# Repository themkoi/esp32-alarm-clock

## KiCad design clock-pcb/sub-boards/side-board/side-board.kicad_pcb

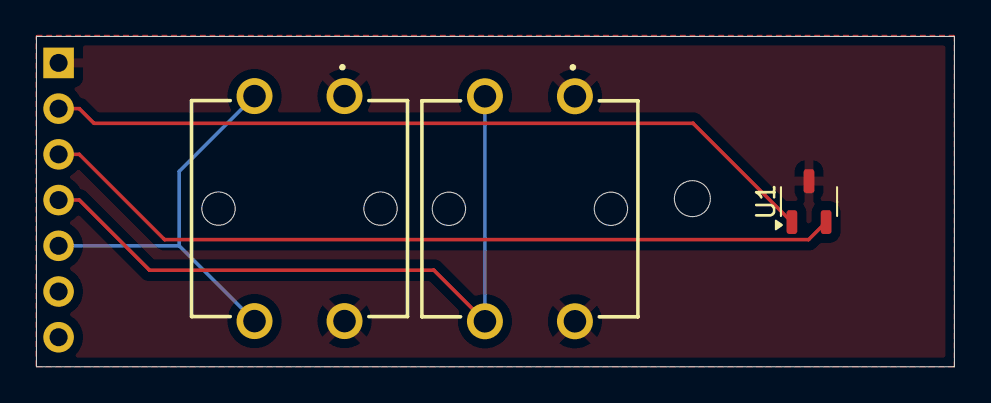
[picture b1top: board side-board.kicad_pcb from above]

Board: 2 copper layers, 51.0 x 18.3 mm, 4 parts (1 on the bottom side), 5 nets.

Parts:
J1: Conn_01x07_Socket; PinHeader_1x07_P2.54mm_Horizontal
S1, S2: B3F-5050; B3F-4055
U1: TMAG5231C1GQDBZR; SOT-23-3

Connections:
+3V3: J1.2, U1.1 (VCC)
GND: J1.1, S1.1 (COM_1), S1.2 (COM_2), S2.1 (COM_1), S2.2 (COM_2), U1.3 (GND)
GPIO14: J1.4, S2.3 (NO_1), S2.4 (NO_2)
GPIO15: J1.5, S1.3 (NO_1), S1.4 (NO_2)
GPIO35: J1.3, U1.2 (OUT)

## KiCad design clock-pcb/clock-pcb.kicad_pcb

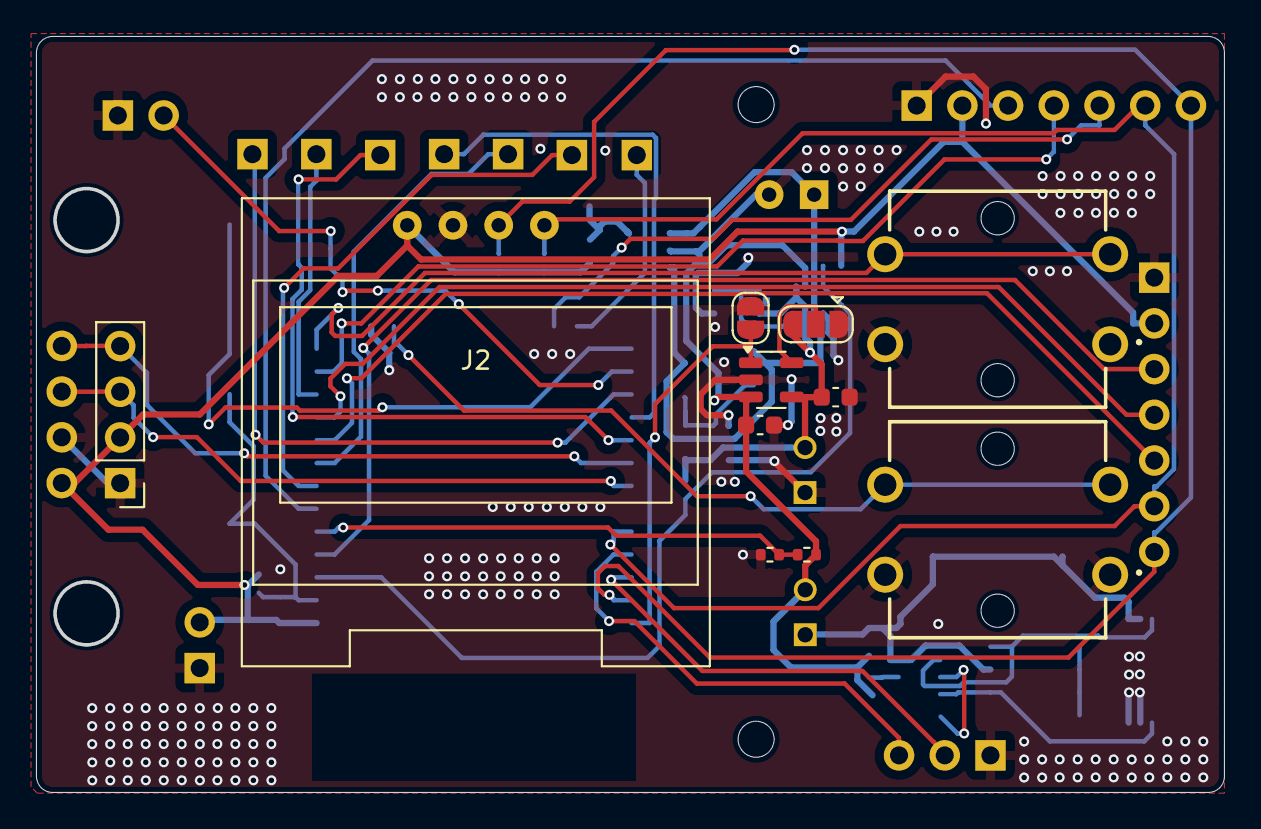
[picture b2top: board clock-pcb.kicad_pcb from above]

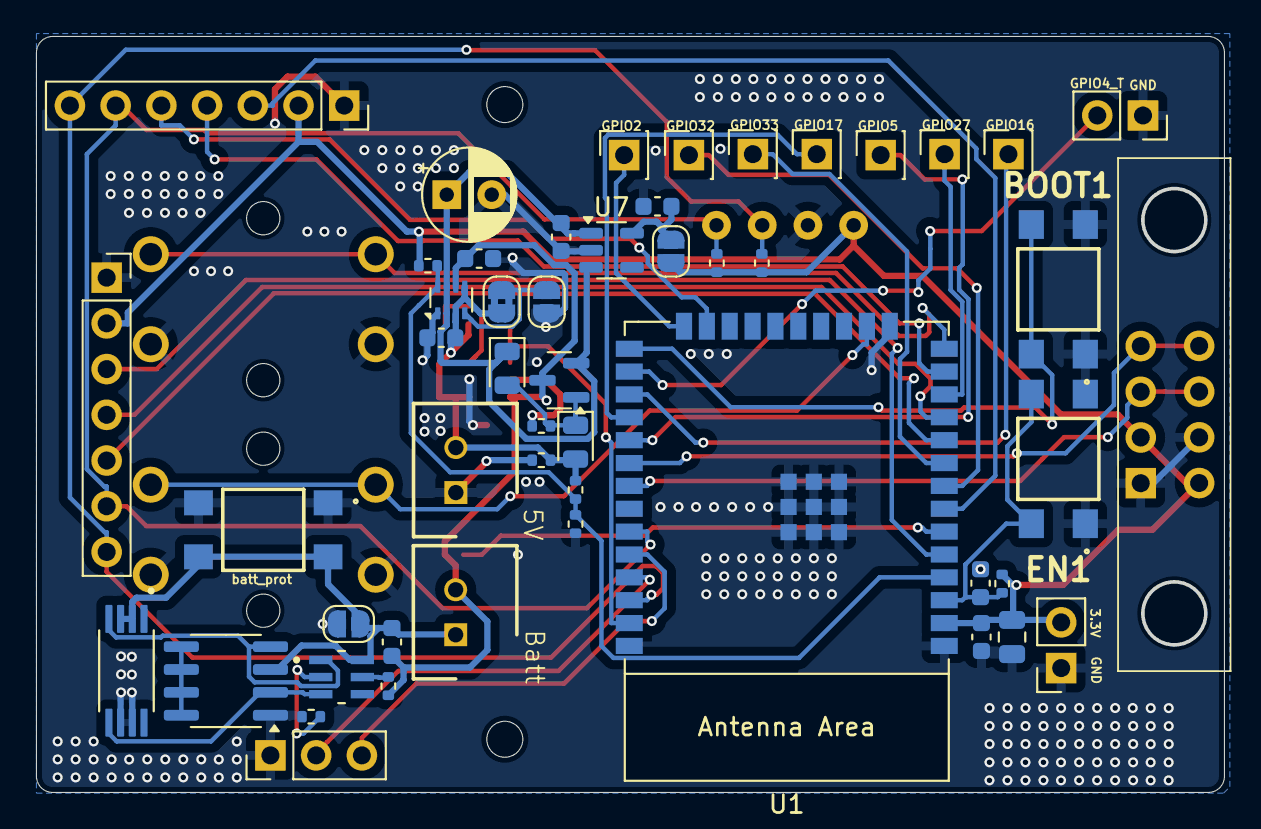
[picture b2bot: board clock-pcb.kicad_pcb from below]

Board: 2 copper layers, 66.0 x 42.0 mm, 61 parts (49 on the bottom side), 42 nets.

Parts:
AO9926C1: SOIC-8_3.9x4.9mm_P1.27mm
BATT_P1: TL3305AF160QG
BOOT1: TL3305AF160QG
C1: 22uF; C_0805_2012Metric
C2, C3, C4: 0.1uF; C_0603_1608Metric
C5: 100uF; CP_Radial_D5.0mm_P2.50mm
C6, C7, C8, C9, C10, C11: 1uF; C_0603_1608Metric
D3, D4: SD0805S040S0R5; D_0805_2012Metric
EN1: TL3305AF160QG
J1: Conn_01x03_Pin; PinHeader_1x03_P2.54mm_Vertical
J2: oled; SSD1306_0.96_Oled
J3: Led display; tm1637_module
J4: Led display 2; PinHeader_1x04_P2.54mm_Vertical
J5, J6: Conn_01x07_Socket; PinSocket_1x07_P2.54mm_Vertical
J7, J9, J10, J11, J12, J13, J14: Conn_01x01_Socket; PinSocket_1x01_P2.54mm_Vertical
J8, J15: Conn_01x02_Socket; PinSocket_1x02_P2.54mm_Vertical
JP1, JP2, JP7: Jumper; SolderJumper-2_P1.3mm_Open_RoundedPad1.0x1.5mm
JP3: Jumper_bridged; SolderJumper-2_P1.3mm_Bridged2Bar_RoundedPad1.0x1.5mm
JP4: SolderJumper_3_Open; SolderJumper-3_P1.3mm_Open_RoundedPad1.0x1.5mm
JP5: SolderJumper_2_Open; SolderJumper-2_P1.3mm_Open_RoundedPad1.0x1.5mm
Q1: FS8205A; SOP65P640X120-8N
Q2: FDN304PZ; SOT-23
R1: 10k; R_0402_1005Metric
R2: 300k; R_0402_1005Metric
R3, R10: 800k; R_0402_1005Metric
R4: 330R; R_0402_1005Metric
R5: 2.7K; R_0402_1005Metric
R6: 10K; R_0402_1005Metric
R7: 500k; R_0402_1005Metric
R8: 100K; R_0402_1005Metric
R9: 50k; R_0402_1005Metric
R11, R12: 5.1k; R_0402_1005Metric
S3, S4: B3F-5050; B3F-4055
U1: ESP32-WROOM-E; ESP32-WROOM-32E
U2: SOT95P280X140-6N
U3: SHDR2W64P0X250_1X2_740X575X700P
U4: TPS2116DRL; SOT-583-8
U5: MCP73811T-420I-OT; SOT-23-5
U7: TLV75533PDBV; SOT-23-5
USB_BOARD1: Conn_01x02_Socket; SHDR2W64P0X250_1X2_740X575X700P

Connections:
+3V3: C1.1, C2.1, J2.1, J3.4, J4.2, J5.2, J6.2, J15.2, JP7.2 (B), R1.1, R6.2, R11.1, R12.1, U1.2 (3V3)
+BATT: C4.2, C7.1, C11.1, Q2.3 (D), R2.1, R4.2, U3.2, U4.6 (VIN2), U5.3 (V_{BAT})
-BATT: AO9926C1.3 (S1), BATT_P1.3, BATT_P1.4, C4.1, JP1.1 (A), Q1.2, Q1.3, U2.6 (VSS), U3.1
ADC_BATT: R2.2, R3.1, U1.6 (GPIO34/ADC1_CH6)
BUTTON_DOWN: S4.3 (NO_1), S4.4 (NO_2), U1.16 (MTCK/GPIO13/ADC2_CH4)
BUTTON_UP: S3.3 (NO_1), S3.4 (NO_2), U1.14 (MTDI/GPIO12/ADC2_CH5)
CHARGE_EN: JP5.2 (B), U1.37 (GPIO23), U5.1 (CE)
CLK: J3.1, J4.4, U1.30 (GPIO18)
CO: AO9926C1.2 (G2), Q1.5, U2.3 (CO)
DIO: J3.2, J4.3, U1.31 (GPIO19)
DO: AO9926C1.4 (G1), Q1.4, U2.1 (DO)
EN: C3.2, EN1.3, EN1.4, R1.2, U1.3 (EN/CHIP_PU)
GND: AO9926C1.1 (S2), BATT_P1.1, BATT_P1.2, BOOT1.1, BOOT1.2, C1.2, C2.2, C3.1, C5.2, C6.1, C7.2, C8.2, C9.2, C10.2, C11.2, EN1.1, EN1.2, J1.1, J2.2, J3.3, J4.1, J5.1, J6.1, J8.1, J15.1, JP1.2 (B), JP2.1 (A), JP4.1 (A), JP5.1 (A), Q1.6, Q1.7, R3.2, R5.2, R8.2, R9.2, R10.2, S3.1 (COM_1), S3.2 (COM_2), S4.1 (COM_1), S4.2 (COM_2), U1.1 (GND), U1.15 (GND), U1.38 (GND), U1.39 (GND_THERMAL), U4.1 (GND), U5.2 (V_{SS}), U7.2 (GND), USB_BOARD1.1
GPIO4_T: J8.2, U1.26 (ADC2_CH0/GPIO4)
GPIO14: J5.4, U1.13 (MTMS/GPIO14/ADC2_CH6)
GPIO15: J5.5, U1.23 (MTDO/GPIO15/ADC2_CH3)
GPIO25: J6.5, U1.10 (DAC_1/ADC2_CH8/GPIO25)
GPIO26: J6.4, U1.11 (DAC_2/ADC2_CH9/GPIO26)
GPIO35: J5.3, U1.7 (GPIO35/ADC1_CH7)
GPIO39: J6.3, U1.5 (SENSOR_VN/GPIO39/ADC1_CH3)
IO0: BOOT1.3, BOOT1.4, U1.25 (GPIO0/BOOT/ADC2_CH1)
LDO_IN: C5.1, C9.1, D4.1 (K), Q2.2 (S), U4.2 (VOUT), U4.7 (VOUT), U7.1 (IN), U7.3 (EN)
unnamed: AO9926C1.5 (D1), AO9926C1.6 (D1), AO9926C1.7 (D2), AO9926C1.8 (D2)
unnamed: D3.1 (K), D4.2 (A), Q2.1 (G), R8.1
unnamed: J7.1, U1.8 (32K_XP/GPIO32/ADC1_CH4)
unnamed: J9.1, U1.29 (GPIO5)
unnamed: J10.1, U1.24 (ADC2_CH2/GPIO2)
unnamed: J11.1, U1.12 (ADC2_CH7/GPIO27)
unnamed: J12.1, U1.27 (GPIO16)
unnamed: J13.1, U1.28 (GPIO17)
unnamed: J14.1, U1.9 (32K_XN/GPIO33/ADC1_CH5)
unnamed: JP2.2 (B), JP3.1 (A), U4.4 (PR1)
unnamed: JP4.2 (C), U5.5 (PROG)
unnamed: C8.1, JP7.1 (A), U7.5 (OUT)
unnamed: R4.1, U2.5 (VDD)
unnamed: R5.1, U2.2 (VM)
POWER_STATUS: R6.1, R7.2, R10.1, U1.4 (SENSOR_VP/GPIO36/ADC1_CH0), U4.8 (ST)
RX: J1.3, U1.34 (U0RXD/GPIO3)
SCL: J2.3, J5.7, J6.7, R11.2, U1.36 (GPIO22)
SDA: J2.4, J5.6, J6.6, R12.2, U1.33 (GPIO21)
TX: J1.2, U1.35 (U0TXD/GPIO1)
VBUS: C6.2, C10.1, D3.2 (A), JP3.2 (B), JP4.3 (B), R7.1, R9.1, U4.3 (VIN1), U4.5 (MODE), U5.4 (V_{DD}), USB_BOARD1.2

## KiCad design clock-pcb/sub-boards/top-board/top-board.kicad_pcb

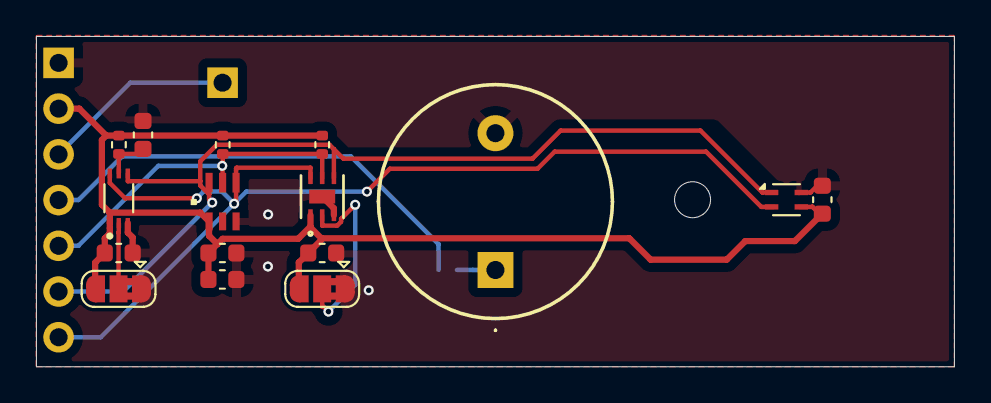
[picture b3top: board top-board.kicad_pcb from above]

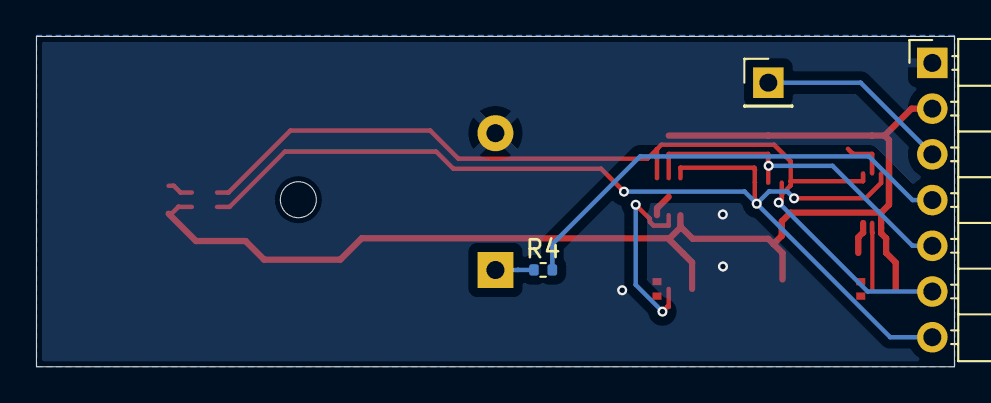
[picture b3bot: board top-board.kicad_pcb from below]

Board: 2 copper layers, 51.0 x 18.3 mm, 19 parts (3 on the bottom side), 11 nets.

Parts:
C1, C2, C3, C5, C6: 0.1uF; C_0603_1608Metric
C4: 4.7uF; C_0603_1608Metric
J1: Conn_01x07_Socket; PinHeader_1x07_P2.54mm_Horizontal
J2: Conn_01x01_Pin; PinHeader_1x01_P2.54mm_Vertical
JP1, JP2: SolderJumper_3_Bridged12; SolderJumper-3_P1.3mm_Bridged2Bar12_RoundedPad1.0x1.5mm
L1: CPT-14146-80T; CPT1414680T
R1: 1K; R_0402_1005Metric
R2, R3: 10K; R_0402_1005Metric
R4: 330R; R_0402_1005Metric
U1: BH1750FVI-TR; XDCR_BH1750FVI-TR
U2: LTR-F216A
U3: OPT3004DTSR; DNP6_TEX
U4: SHT4x; Sensirion_DFN-4_1.5x1.5mm_P0.8mm_SHT4x_NoCentralPad

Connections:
+3V3: C2.1, C3.1, C4.1, C5.1, C6.2, J1.2, JP1.3 (B), JP2.3 (B), R1.2, R2.1, R3.1, U1.1 (VCC), U2.1 (VDD), U3.1 (VDD), U4.3 (VDD)
GND: C1.2, C2.2, C3.2, C4.2, C5.2, C6.1, J1.1, JP1.1 (A), JP2.1 (A), L1.2, U1.3 (GND), U2.3 (GND), U3.3 (GND), U3.7 (EPAD), U4.4 (VSS)
GPIO25: J1.5, R2.2, R3.2, U2.5 (INT), U3.5 (INT)
GPIO26: J1.4, R4.2
GPIO39: J1.3, J2.1
unnamed: JP1.2 (C), U1.2 (ADDR)
unnamed: JP2.2 (C), U3.2 (ADDR)
unnamed: L1.1, R4.1
unnamed: C1.1, R1.1, U1.5 (DVI)
SCL: J1.7, U1.6 (SCL), U2.4 (SCL), U3.6 (SDA), U4.2 (SCL)
SDA: J1.6, U1.4 (SDA), U2.6 (SDA), U3.4 (SCL), U4.1 (SDA)

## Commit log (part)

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2025-02-12 support for touch "slider"
2025-02-12 les lag on screensaver
2025-02-12 debugging
2025-02-13 fix stupid bug of not chaning alarm menu
2025-02-13 make input detection more responsive and led brightness
2025-02-13 uh why isnt it working?
2025-02-20 I fogor
2025-02-20 fix alarm menu
2025-02-20 fix dimming sometimes not working
2025-02-24 fixing some bugs writing comments and cleaning up
2025-02-24 get rid of unnecesary define left over from using menu library
2025-02-24 another unnecesary define
2025-03-01 try fix
2025-03-08 work with longer menu names
2025-03-21 alarm menu adjustment
2025-03-23 "fixed" weather not working sometimes and more responsive display wakeup
2025-03-23 comment
2025-03-23 adjust behavior on battery
2025-03-24 why did I accidentally remove this
2025-03-25 timezone
2025-03-26 uh alarm change
2025-03-29 more responsive main page
2025-03-29 better battery stuff
2025-03-30 forgot to resume task
2025-04-03 one alarm multple days
2025-04-03 toggle
2025-04-11 better touch management
2025-04-17 interface
2025-04-21 expose mmwave
2025-04-21 platformio
2025-05-05 optimize
2025-05-17 littlefs some bug fixes alarm interface fix
2025-05-17 uh show menu
2025-05-17 less logs should be more responsive?
2025-05-18 working buttons
2025-05-18 touch finally kill me
2025-05-18 Long press alarm change
2025-05-18 icons
2025-05-18 memory
2025-05-18 crashing
2025-05-19 led display
2025-05-19 ui fix interface fix holding support
2025-05-19 fix input detection
2025-05-19 continue even if something goes wrong
2025-05-21 fix stack overflow
2025-05-21 uh touch stuff
2025-05-23 touch stuff
2025-05-23 alarms stuff
2025-06-12 fix battery managment still need to recabrate touch
2025-06-12 fix reading charts
2025-06-13 sleeping
2025-06-21 check if the menu has been deleted before changing name
2025-06-21 recalibrate touch sleep
2025-07-01 alarms
2025-07-01 light alarms
2025-07-02 initialize manage alarms
2025-07-02 general fixes and clean up
2025-07-02 fix turning off alarm I think
2025-07-24 ui glitches fix better button management and second alarm melody and remember selection from last menu
2025-07-25 clean up code
2025-07-26 fix resetting menu and clean up unused stuff
